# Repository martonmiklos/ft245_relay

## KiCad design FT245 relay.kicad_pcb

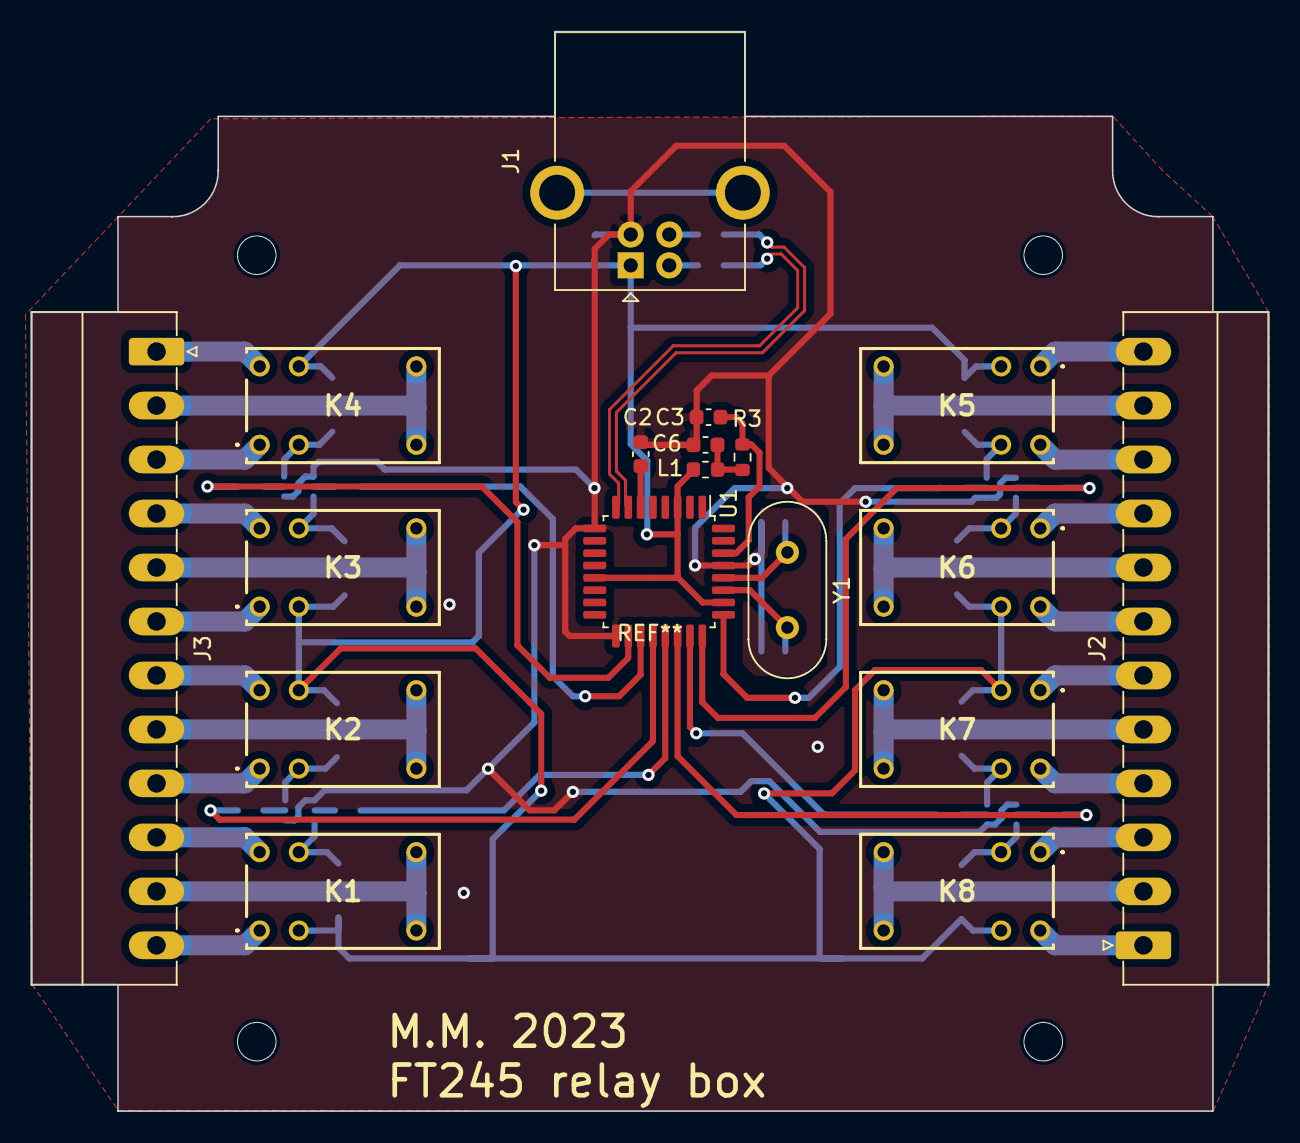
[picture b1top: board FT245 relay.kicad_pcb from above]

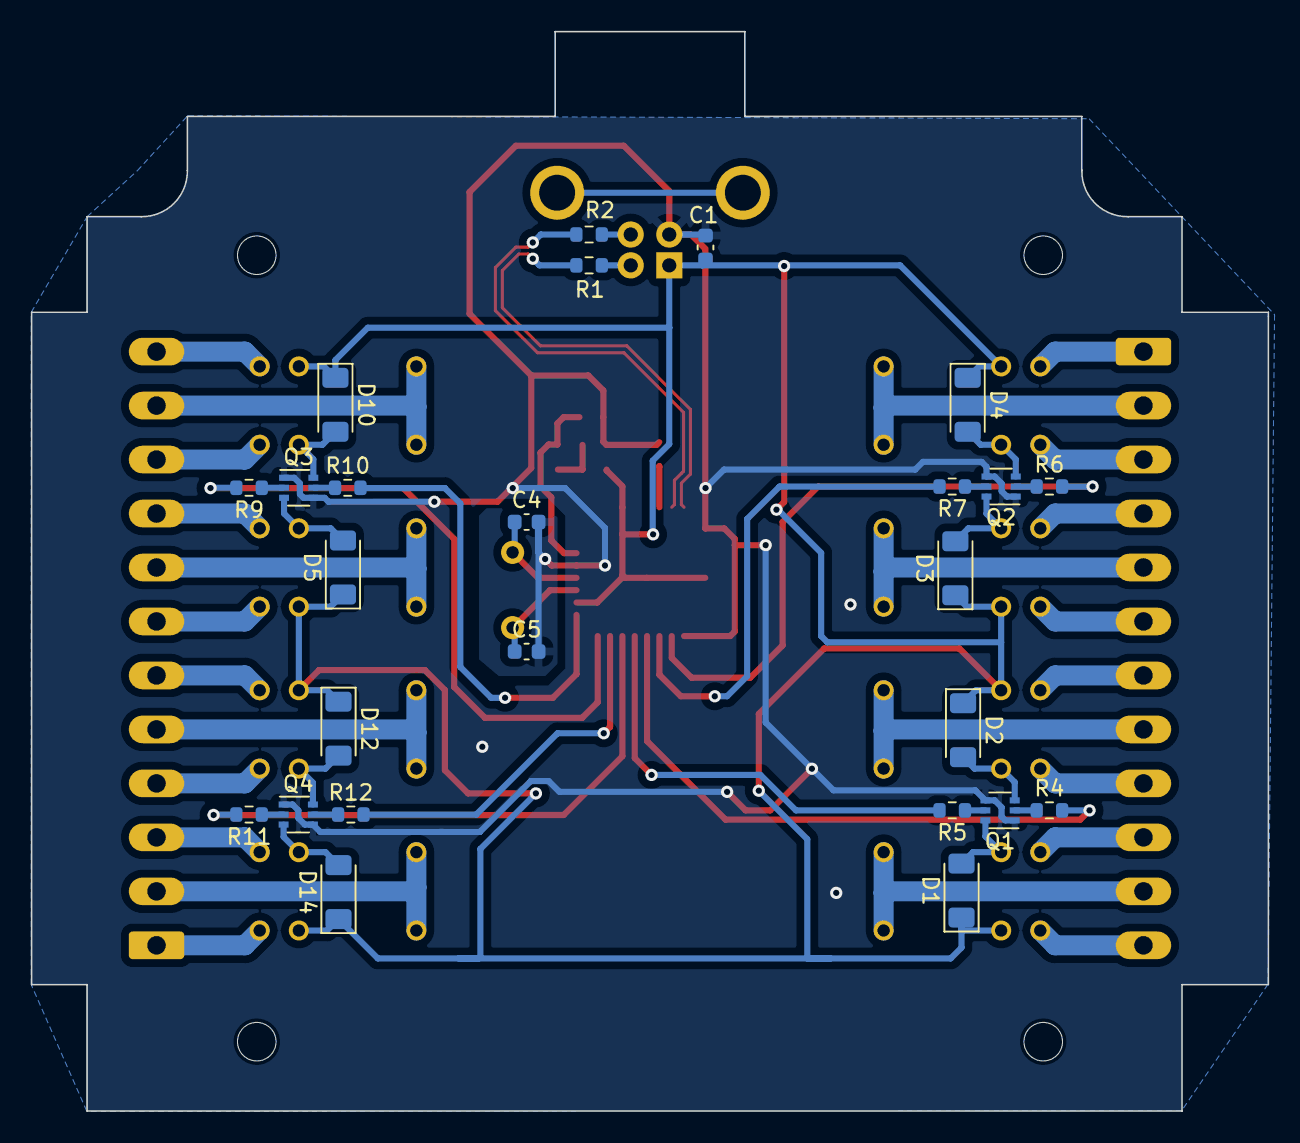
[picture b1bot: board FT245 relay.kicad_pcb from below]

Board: 2 copper layers, 80.2 x 70.0 mm, 43 parts (25 on the bottom side), 59 nets.

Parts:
C1: 10nF; C_0603_1608Metric
C2: 33nF; C_0603_1608Metric
C3: 100nF; C_0603_1608Metric
C4, C5: 27pF; C_0603_1608Metric
C6: 4u7; C_0603_1608Metric
D1, D2, D3, D4, D5, D10, D12, D14: LL4148; D_MiniMELF
J1: USB_B; USB_B_OST_USB-B1HSxx_Horizontal
J2, J3: Conn_01x12_Pin; PhoenixContact_MC_1,5_12-G-3.5_1x12_P3.50mm_Horizontal
K1, K2, K3, K4, K5, K6, K7, K8: SY-5-K; SY5K
L1: L_Ferrite; L_0603_1608Metric
Q1, Q2, Q3, Q4: BC847BS; SOT-363_SC-70-6
R1, R2: 27; R_0603_1608Metric
R3: 470; R_0603_1608Metric
R4, R5, R6, R7, R9, R10, R11, R12: 1K; R_0603_1608Metric
U1: FT245BM; LQFP-32_7x7mm_P0.8mm
Y1: 6 MHz; Crystal_HC49-4H_Vertical

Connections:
+3.3V: C2.1, U1.6 (3V3OUT)
+5V: C1.1, D1.1 (K), D2.1 (K), D3.1 (K), D4.1 (K), D5.1 (K), D10.1 (K), D12.1 (K), D14.1 (K), J1.1 (VBUS), K1.2 (COIL_1), K2.9 (COIL_2), K3.2 (COIL_1), K4.9 (COIL_2), K5.2 (COIL_1), K6.9 (COIL_2), K7.2 (COIL_1), K8.9 (COIL_2), L1.2, U1.3 (VCC), U1.13 (VCCIO), U1.26 (VCC)
/D_N: J1.2 (D-), R1.2
/D_P: J1.3 (D+), R2.2
/D_R_N: R1.1, U1.8 (USBDM)
/D_R_P: R2.1, U1.7 (USBDP)
/RELAY0: R10.2, U1.25 (D0)
/RELAY1: R9.2, U1.24 (D1)
/RELAY2: R12.2, U1.23 (D2)
/RELAY3: R11.2, U1.22 (D3)
/RELAY4: R5.2, U1.21 (D4)
/RELAY5: R4.2, U1.20 (D5)
/RELAY6: R7.2, U1.19 (D6)
/RELAY7: R6.2, U1.18 (D7)
/VBUS_FILTERED: C6.1, L1.1, R3.2
GND: C1.2, C2.2, C3.2, C4.2, C5.2, C6.2, J1.4 (GND), Q1.1 (E1), Q1.4 (E2), Q2.1 (E1), Q2.4 (E2), Q3.1 (E1), Q3.4 (E2), Q4.1 (E1), Q4.4 (E2), U1.9 (GND), U1.17 (GND), U1.29 (GND)
unnamed: D1.2 (A), K1.9 (COIL_2), Q1.6 (C1)
unnamed: D2.2 (A), K2.2 (COIL_1), Q1.3 (C2)
unnamed: D3.2 (A), K3.9 (COIL_2), Q2.6 (C1)
unnamed: D4.2 (A), K4.2 (COIL_1), Q2.3 (C2)
unnamed: D5.2 (A), K6.2 (COIL_1), Q3.3 (C2)
unnamed: D10.2 (A), K5.9 (COIL_2), Q3.6 (C1)
unnamed: D12.2 (A), K7.9 (COIL_2), Q4.6 (C1)
unnamed: D14.2 (A), K8.2 (COIL_1), Q4.3 (C2)
unnamed: J2.1, K8.10 (NO)
unnamed: J2.2, K8.5 (COM_1), K8.6 (COM_2)
unnamed: J2.3, K8.1 (NC)
unnamed: J2.4, K7.10 (NO)
unnamed: J2.5, K7.5 (COM_1), K7.6 (COM_2)
unnamed: J2.6, K7.1 (NC)
unnamed: J2.7, K6.10 (NO)
unnamed: J2.8, K6.5 (COM_1), K6.6 (COM_2)
unnamed: J2.9, K6.1 (NC)
unnamed: J2.10, K5.10 (NO)
unnamed: J2.11, K5.5 (COM_1), K5.6 (COM_2)
unnamed: J2.12, K5.1 (NC)
unnamed: J3.1, K4.10 (NO)
unnamed: J3.2, K4.5 (COM_1), K4.6 (COM_2)
unnamed: J3.3, K4.1 (NC)
unnamed: J3.4, K3.10 (NO)
unnamed: J3.5, K3.5 (COM_1), K3.6 (COM_2)
unnamed: J3.6, K3.1 (NC)
unnamed: J3.7, K2.10 (NO)
unnamed: J3.8, K2.5 (COM_1), K2.6 (COM_2)
unnamed: J3.9, K2.1 (NC)
unnamed: J3.10, K1.10 (NO)
unnamed: J3.11, K1.5 (COM_1), K1.6 (COM_2)
unnamed: J3.12, K1.1 (NC)
unnamed: Q1.2 (B1), R4.1
unnamed: Q1.5 (B2), R5.1
unnamed: Q2.2 (B1), R6.1
unnamed: Q2.5 (B2), R7.1
unnamed: Q3.2 (B1), R9.1
unnamed: Q3.5 (B2), R10.1
unnamed: Q4.2 (B1), R11.1
unnamed: Q4.5 (B2), R12.1
unnamed: C3.1, R3.1, U1.30 (AVCC)
unnamed: C5.1, U1.27 (XTIN), Y1.2
unnamed: C4.1, U1.28 (XTOUT), Y1.1

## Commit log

2023-03-09 Initial add
